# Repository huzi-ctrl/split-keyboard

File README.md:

# PKB — Wireless Split Mechanical Keyboard

**PKB (Printed KeyBoard)** is a custom 42-key wireless split mechanical keyboard designed from scratch in KiCad 10 and SolidWorks, powered by dual **Seeed Studio XIAO nRF52840** microcontrollers running **ZMK Firmware**.

---

## Why I Made It & How It Works

### Why I Built PKB
Traditional keyboards force your wrists to angle inward and make your fingers stretch across 6+ rows to reach numbers, symbols, and navigation keys. I wanted to design a compact, fully wireless split keyboard where:
1. Each half can be positioned at shoulder width for natural ergonomics.
2. Every letter, symbol, bracket, arrow key, F-key, and Numpad key is within **one row of the home row** using 3 tap-dance layers (**126 effective key bindings** across 42 physical switches).
3. Both halves fit on a **single panelized PCB** connected by mouse-bite breakaway tabs (`BO1`–`BO3`) to make fabrication and assembly clean and cost-effective.

### How It Works
- **Microcontroller & Wireless Split (`Seeed Studio XIAO nRF52840`)**: Each half runs a XIAO nRF52840 (`U1`/`U2`). The left half acts as the central controller (connecting to up to 4 devices over Bluetooth Low Energy or USB-C), while the right half pairs wirelessly over BLE to the left half.
- **I2C GPIO Expansion (`PCF8574AP`)**: Because the XIAO nRF52840 has only 11 GPIO pins, the 5 matrix columns (`COL0`–`COL4`) are driven directly by the XIAO (`D1`–`D5`), while the 5 matrix rows (`ROW0`–`ROW4`) are read through an **NXP PCF8574AP** 8-bit I2C I/O expander (`U3`/`U4`) on a shared I2C bus (`SCL` on `D9`, `SDA` on `D10`).
- **Dual 128×32 OLED Status Displays (`J3`/`J4`)**: Each half includes an I2C SSD1306 128×32 OLED display showing live battery percentage (`%`), active layer name (`QWERTY`, `CODE / NAV`, `NUM / FN`), and USB/Bluetooth profile status, with automatic 30-second idle blanking.
- **Per-Key RGB Underglow (`42× SK6812MINI`) with High-Side MOSFET Power Cut (`Q1`–`Q4`)**: Each half features 21 addressable SK6812MINI LEDs driven by hardware SPI (`D0`) and powered from `VBAT` through an NMOS+PMOS (`Q1`/`Q3`, `Q2`/`Q4`) high-side load switch (`D8`) so LED quiescent draw can be completely cut off to preserve battery life.

---

## PCB & 3D Renders

### Full Panelized PCB Layout (KiCad)

### 3D PCB Render

---

## Schematics

Both the left and right halves share a modular hierarchical schematic (`side.kicad_sch`):

### Left Half Schematic (`/left/`)

### Right Half Schematic (`/right/`)

---

## CAD & Enclosure Design

Custom 3D-printed enclosures modeled in SolidWorks with integrated battery compartment and cable routing channel (available in `.STEP`, `.SLDPRT`, and `.3MF` formats inside [`CAD/`](CAD/)):

| Left Half Enclosure (`left_cad.png`) | Right Half Enclosure (`right_cad.png`) |
| :---: | :---: |
|  |  |

---

## Hardware Pinout

| Function | XIAO nRF52840 Pin | Peripheral / Notes |
| :--- | :--- | :--- |
| **`DLED` (RGB Data)** | `D0` (`P0.02`) | 21× SK6812MINI addressable RGB LEDs per half (`&spi2` MOSI via 330 $\Omega$ resistor) |
| **`COL0` – `COL4`** | `D1` – `D5` (`P0.03`, `P0.28`, `P0.29`, `P0.04`, `P0.05`) | Matrix column outputs (`GPIO_ACTIVE_LOW`, `col2row`) |
| **`INT` (Expander Interrupt)** | `D6` (`P1.11`) | Connected to `PCF8574AP` `/INT` (Pin 13) |
| **`VLED` Power Switch** | `D8` (`P1.13`) | Drives NMOS $\rightarrow$ PMOS high-side switch for `VLED` (`ext-power`) |
| **`SCL` (I2C Clock)** | `D9` (`P1.14`) | `i2c0` (`&xiao_i2c`) with 4.7 k$\Omega$ pull-up to `+3V3` |
| **`SDA` (I2C Data)** | `D10` (`P1.15`) | `i2c0` (`&xiao_i2c`) with 4.7 k$\Omega$ pull-up to `+3V3` |
| **`ROW0` – `ROW4`** | `PCF8574AP` `P0` – `P4` | I2C I/O Expander at address `0x38` (`A0=A1=A2=GND`) |
| **OLED Display (`J3`/`J4`)** | I2C (`SCL`/`SDA`) | 128×32 SSD1306 OLED at address `0x3C` |

---

## Firmware & Keymap (`ZMK`)

Pre-built `.uf2` firmware binaries are automatically compiled by GitHub Actions and published to [**GitHub Releases**](https://github.com/huzi-ctrl/zmk-config-split-keyboard/releases/latest):
- **Left Half (Central):** `pkb_left-seeeduino_xiao_ble-zmk.uf2`
- **Right Half (Peripheral):** `pkb_right-seeeduino_xiao_ble-zmk.uf2`

### Tap-Dance Thumb Keys
- **Left Thumb**: `1 Tap` = **Space** | `2 Taps` = Toggle **Layer 1 (`CODE / NAV`)**
- **Right Thumb**: `1 Tap` = **Backspace** | `2 Taps` = Toggle **Layer 2 (`NUM / FN`)**

### Layer 0: `QWERTY` (Base)
```text
+-----------------------------------------+   +-----------------------------------------+
|   Q   |   W   |   E   |   R   |   T     |   |   Y   |   U   |   I   |   O   |   P     |
|   A   |   S   |   D   |   F   |   G     |   |   H   |   J   |   K   |   L   |   ;     |
|   Z   |   X   |   C   |   V   |   B     |   |   N   |   M   |   ,   |   .   |   /     |
| LCTRL | LSHFT | LALT  | LGUI  |  ESC    |   | RGUI  | RALT  | RSHFT | RCTRL | ENTER   |
+-------------------------------+---------+   +---------+-------------------------------+
                                | SPC/NAV |   | BSP/NUM |
                                +---------+   +---------+
```

### Layer 1: `CODE / NAV` (Double-Tap Left Thumb)
```text
+-----------------------------------------+   +-----------------------------------------+
|   `   |   [   |   ]   |   -   |   =     |   | PG_UP | HOME  |  UP   |  END  |  DEL    |
|   ~   |   {   |   }   |   _   |   +     |   | PG_DN | LEFT  | DOWN  | RIGHT |  ---    |
|  ---  |   \   |   |   |   <   |   >     |   |  ---  |  ---  |  ---  |  ---  |  ---    |
|  ---  |  ---  |  ---  |  ---  |  ---    |   |  ---  |  ---  |  ---  |  ---  |  ---    |
+-------------------------------+---------+   +---------+-------------------------------+
                                | SPC/NAV |   |   ---   |
                                +---------+   +---------+
```

### Layer 2: `NUM / FN` (Double-Tap Right Thumb)
```text
+-----------------------------------------+   +-----------------------------------------+
|  F1   |  F2   |  F3   |  F4   |  F5     |   |   /   |   7   |   8   |   9   |   -     |
|  F6   |  F7   |  F8   |  F9   |  F10    |   |   *   |   4   |   5   |   6   |   +     |
|  F11  |  F12  |RGB_TOG|EP_TOG |OUT_TOG  |   |   0   |   1   |   2   |   3   |   .     |
| BT 1  | BT 2  | BT 3  | BT 4  | BT_CLR  |   |  ---  |  ---  |  ---  |  ---  |  ---    |
+-------------------------------+---------+   +---------+-------------------------------+
                                |   ---   |   | BSP/NUM |
                                +---------+   +---------+
```

---

## Build & Assembly Guide

### Step 1: Depanelize the PCB
1. The left and right keyboard halves are manufactured as a single panel joined by three mouse-bite breakaway tabs (`BO1`, `BO2`, `BO3`) along the center spine.
2. Gently flex or snip along the perforated mouse-bite slots using flush cutters to separate the **Left** and **Right** PCBs, then lightly sand the tab edges flush.

### Step 2: Solder Reverse-Mount RGB LEDs (`D63`–`D104`)
1. Flip the PCB to the **bottom (`B.Cu`)** layer.
2. Solder the 21× **SK6812MINI-E** reverse-mount addressable RGB LEDs per half so their lenses shine upward through the rectangular switch LED cutouts.
   - **Important**: Align the notched/beveled corner (`Pin 3 = GND`) of each SK6812MINI-E with the silkscreen marker on the PCB.
   - Use a temperature-controlled soldering iron at **$280\text{--}300\,^\circ\text{C}$** (or low-temp solder paste + hot air) to avoid overheating the plastic LED packages.

### Step 3: Solder Matrix Diodes (`D1`–`D42`) & SMD MOSFETs (`Q1`–`Q4`)
1. **Matrix Diodes (`D1`–`D42`)**: The `ComboDiode` footprints support either **1N4148W (SOD-123 SMD)** diodes on `F.Cu` or `B.Cu`, or **1N4148 (DO-35 through-hole)** diodes. Orient every diode's cathode band (`|◁`) toward the square pad (`K`).
2. **High-Side LED Power Switch (`Q1`–`Q4`)**: Solder the SOT-23 NMOS (`Q1`, `Q2`) and PMOS (`Q3`, `Q4`) transistors onto their designated SMD pads near the microcontroller area on each half.

### Step 4: Solder Passive Components & IC Expanders (`U3`, `U4`)
1. Solder the **100 nF decoupling capacitors** (`C1`–`C42`) next to each RGB LED, plus the **100 µF bulk radial capacitors** (`C43`, `C44`) across the `VLED` power rails.
2. Solder the axial resistors on each half:
   - **$4.7\text{ k}\Omega$** (`R1`–`R6`): I2C `SDA`/`SCL` pull-ups and `/INT` pull-ups.
   - **$10\text{ k}\Omega$** (`R7`, `R8`) & **$100\text{ k}\Omega$** (`R9`, `R10`): MOSFET gate bias/pull-down resistors.
   - **$330\text{ }\Omega$** (`R11`, `R12`): RGB `DIN` data-line series resistors.
3. Solder the **PCF8574AP** DIP-16 I2C I/O expanders (`U3`, `U4`)—or DIP-16 IC sockets—ensuring the Pin 1 half-moon notch matches the PCB silkscreen.

### Step 5: Solder Hot-Swap Sockets, Switches & Peripherals
1. **Kailh MX Hot-Swap Sockets (`SW1`–`SW42`)**: On the **bottom (`B.Cu`)** side of the PCB, solder all 42 Kailh Choc/MX hot-swap sockets onto their wide SMD pads, making sure they sit flat against the board and do not obstruct the switch center hole.
2. **Seeed Studio XIAO nRF52840 (`U1`, `U2`)**:
   - Before soldering the XIAO down, solder two short wire leads onto the **battery `+` and `-` pads** on the underside of the XIAO nRF52840 and route them to the PCB's battery input pads (`J1`/`J2`) and slide power switch (`SW43`/`SW44`).
   - Solder the XIAO nRF52840 onto the PCB using pin headers or low-profile Mill-Max sockets with the USB-C port facing outward toward the top edge of the board.
3. **128×32 SSD1306 OLED Display (`J3`, `J4`)**: Solder the 4-pin OLED header (`GND`, `VCC`, `SCL`, `SDA`) so the OLED sits above the XIAO footprint.
4. **Slide Power Switch (`SW43`, `SW44`) & LiPo Battery (`J1`, `J2`)**: Solder the 3-pin slide switch and the 2-pin JST-PH 2.0 mm battery connector.

### Step 6: Flash ZMK Firmware & Pair Halves
1. Download the latest `.uf2` files from [**GitHub Releases**](https://github.com/huzi-ctrl/zmk-config-split-keyboard/releases/latest):
   - `pkb_left-seeeduino_xiao_ble-zmk.uf2`
   - `pkb_right-seeeduino_xiao_ble-zmk.uf2`
2. Connect the **Left XIAO nRF52840** to your computer via USB-C and **double-click its onboard Reset button**—it will mount as a removable drive named `XIAO-SENSE`.
3. Drag and drop `pkb_left-seeeduino_xiao_ble-zmk.uf2` onto the drive. Repeat with `pkb_right-seeeduino_xiao_ble-zmk.uf2` on the **Right XIAO nRF52840**.
4. Power both halves on at the same time; they will automatically bond to each other over BLE. Pair your computer or phone to **`PKB`** via Bluetooth!

### Step 7: Final Case Assembly
1. 3D-print [`CAD/3mf/left.3MF`](CAD/3mf/left.3MF) and [`CAD/3mf/right.3MF`](CAD/3mf/right.3MF) in PLA or PETG (`0.2 mm` layer height, 15–20% infill).
2. Place the 3.7 V LiPo battery into the recessed pocket at the base of each printed enclosure and plug it into the JST-PH connector (`J1`/`J2`).
3. Seat the assembled PCB into the enclosure, secure it with M2 screws through the mounting holes, press your 42 MX mechanical switches into the hot-swap sockets, and install your keycaps!

---

## Repository Structure

```text
├── CAD/
│   ├── Keyboard.step          # Full 3D assembly in STEP format
│   ├── 3mf/                   # Printable 3MF files (left.3MF, right.3MF)
│   └── Raw/                   # Native SolidWorks part files (left.SLDPRT, right.SLDPRT)
├── kicad/
│   ├── Keyboard.kicad_pro     # KiCad 10 project file
│   ├── Keyboard.kicad_sch     # Top-level schematic sheet
│   ├── side.kicad_sch         # Left/Right modular keyboard half schematic
│   └── Keyboard.kicad_pcb     # Panelized 2-layer PCB layout
├── firmware/
│   ├── boards/shields/pkb/    # ZMK shield definition, devicetree, Kconfig, and C init
│   ├── config/                # Keymap and ZMK configuration
│   └── build.yaml             # GitHub Actions build matrix
├── images/                    # PCB, schematic, and CAD screenshots
└── production.zip             # Ready-to-manufacture Gerber, Drill, and CPL files
```

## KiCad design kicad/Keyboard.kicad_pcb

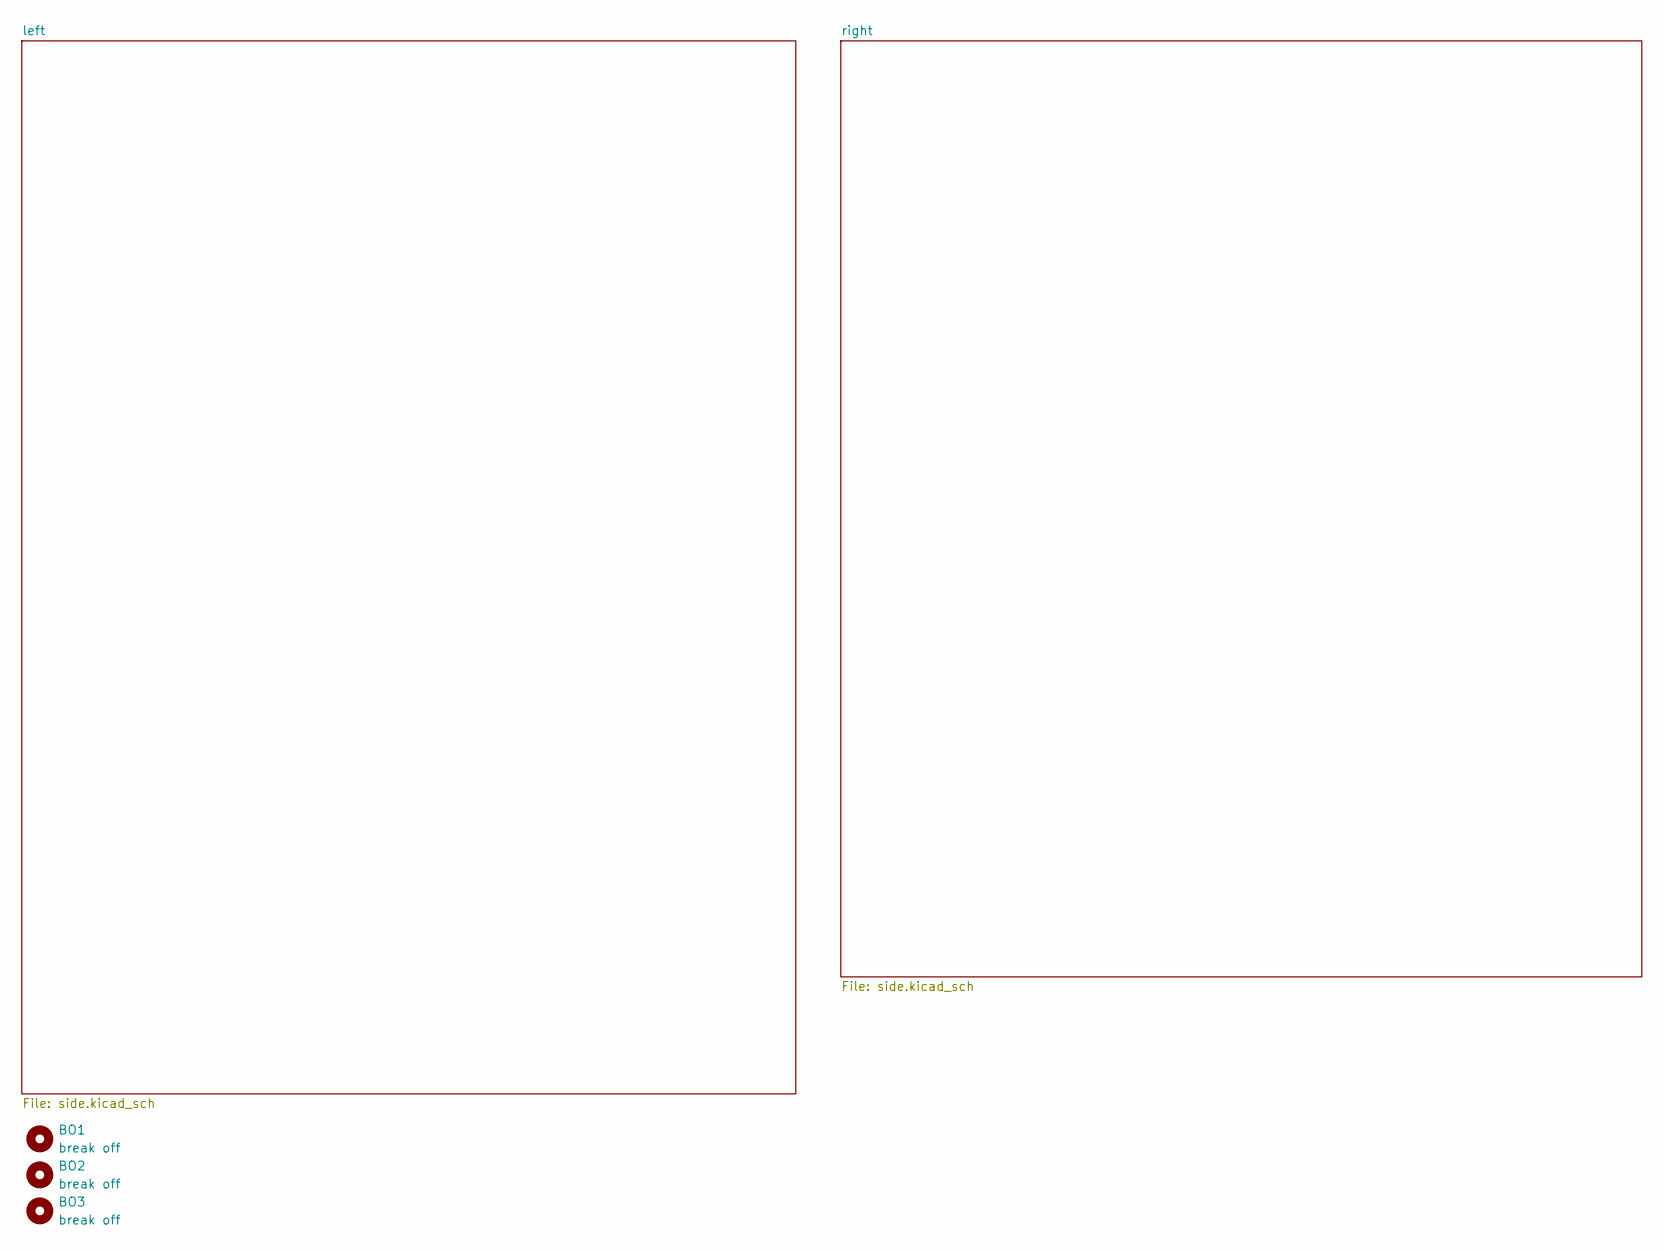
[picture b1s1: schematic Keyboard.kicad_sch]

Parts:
BO1, BO2, BO3: break off; MouseBite-Slot_2.0x4.5mm_outset_D0.5mm_P0.85mm_7h

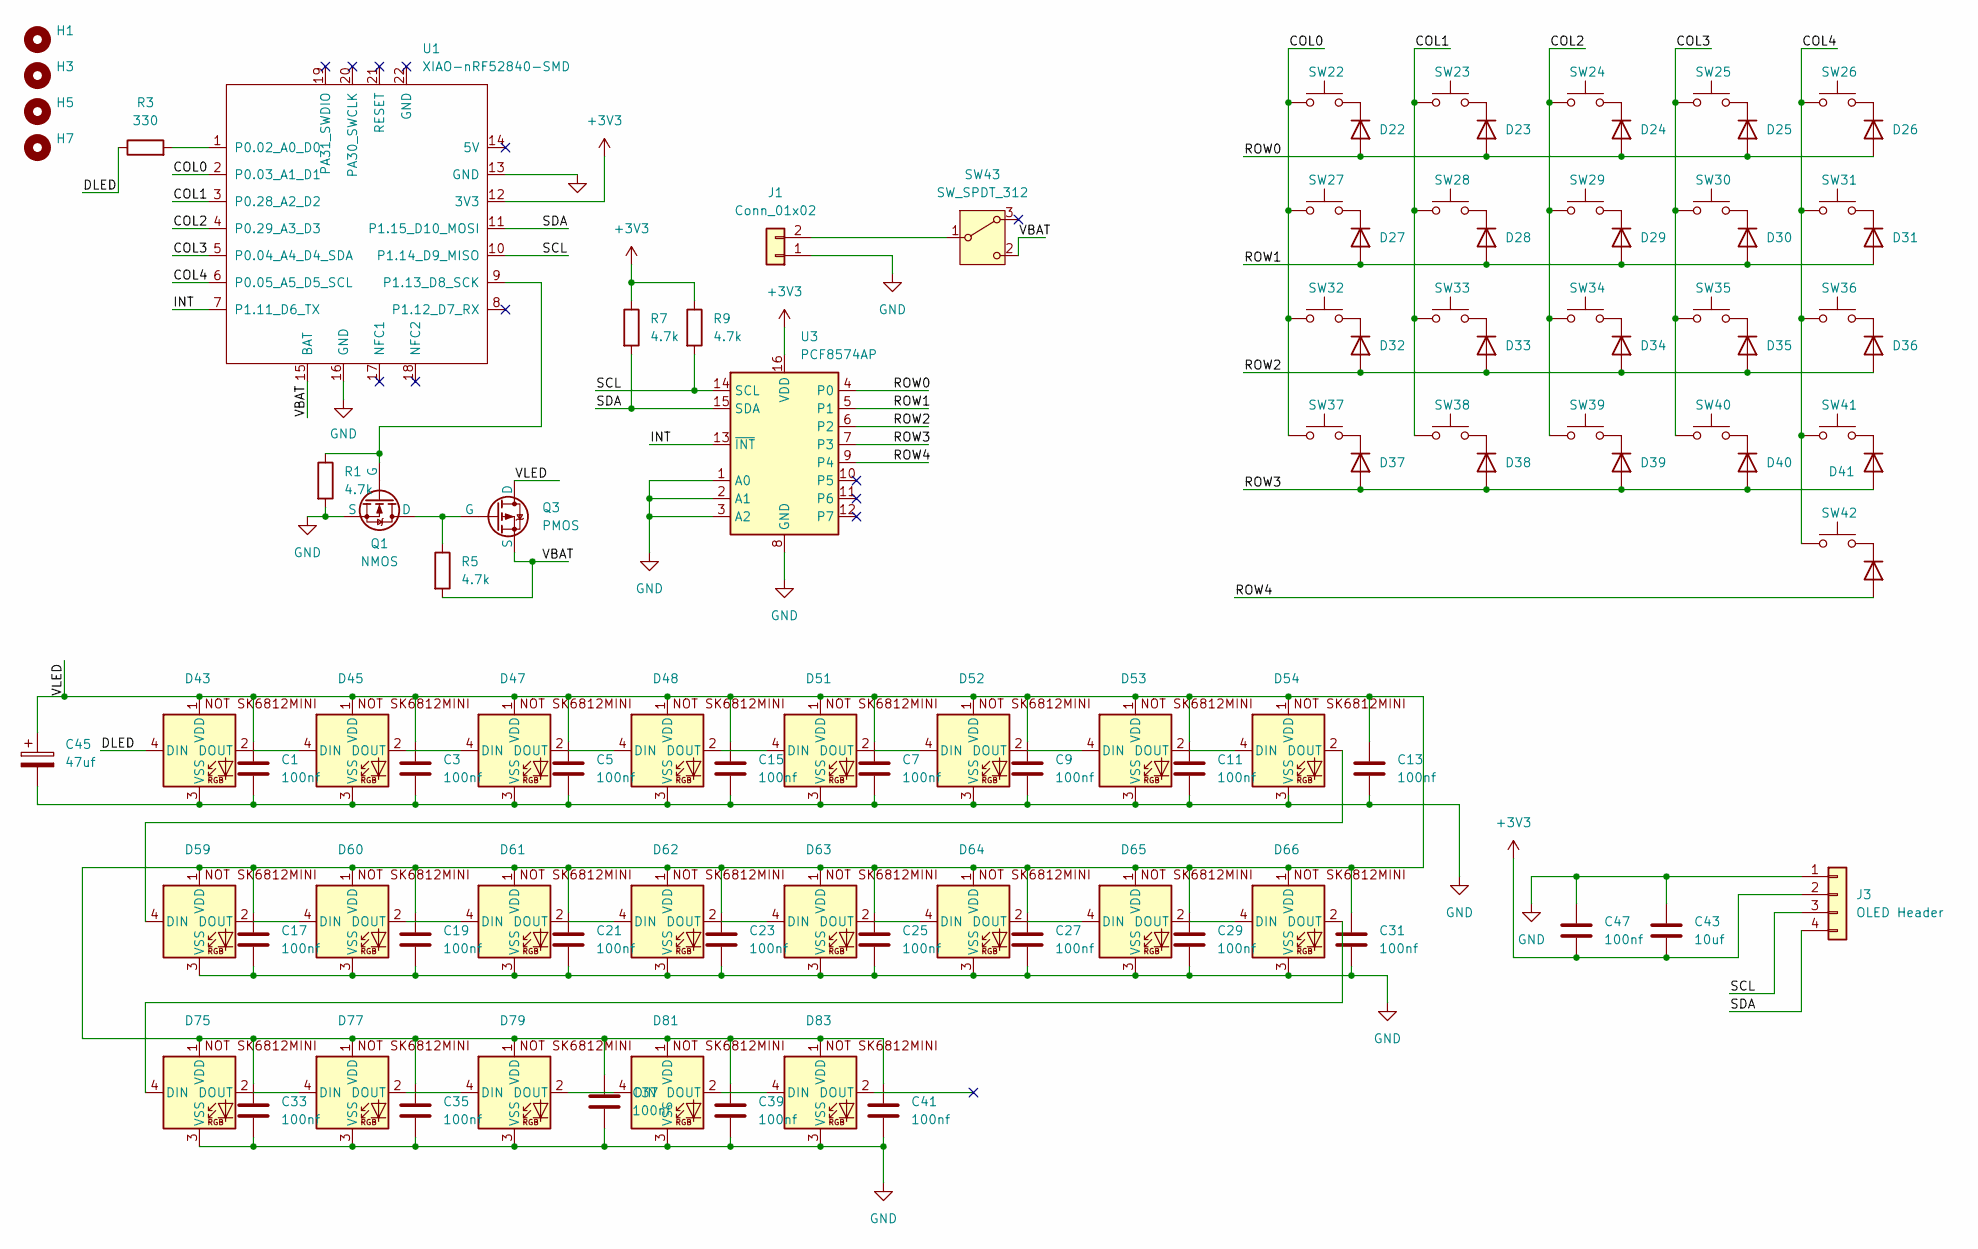
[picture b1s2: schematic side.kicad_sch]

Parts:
C1, C3, C5, C7, C9, C11, C13, C15, C17, C19, C21, C23, C25, C27, C29, C31, C33, C35, C37, C39, C41, C47: 100nf; C_Disc_D5.0mm_W2.5mm_P5.00mm
C43: 10uf; C_Disc_D5.0mm_W2.5mm_P5.00mm
C45: 47uf; CP_Radial_D8.0mm_P3.50mm
D22, D23, D24, D25, D26, D27, D28, D29, D30, D31, D32, D33, D34, D35, D36, D37, D38, D39, D40, D41, D42: D
D43, D45, D47, D48, D51, D52, D53, D54, D59, D60, D61, D62, D63, D64, D65, D66, D75, D77, D79, D81, D83: SK6812MINI-E
H1, H3, H5, H7: MountingHole; MountingHole_2.2mm_M2
J1: Conn_01x02; JST_PH_S2B-PH-K_1x02_P2.00mm_Horizontal
J3: OLED Header; PinSocket_1x04_P2.54mm_Vertical
Q1: NMOS; TO-92-2_Wide
Q3: PMOS; TO-220-3_Vertical
R1, R5, R7, R9: 4.7k; R_Axial_DIN0207_L6.3mm_D2.5mm_P10.16mm_Horizontal
R3: 330; R_Axial_DIN0207_L6.3mm_D2.5mm_P10.16mm_Horizontal
SW22, SW23, SW24, SW25, SW26, SW27, SW28, SW29, SW30, SW31, SW32, SW33, SW34, SW35, SW36, SW37, SW38, SW39, SW40, SW41, SW42: SW_Push
SW43: SW_SPDT_312; PinHeader_1x03_P2.54mm_Vertical
U1: XIAO-nRF52840-SMD; modified-XIAO-nRF52840-SMD
U3: PCF8574AP; DIP-16_W7.62mm

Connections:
+3V3: C43.2, C47.2, J3.2, R7.1, R9.1, U1.12 (3V3), U3.16 (VDD); also elsewhere on the board
/left/COL0: SW22.1, SW27.1, SW32.1, SW37.1, U1.2 (P0.03_A1_D1)
/left/COL1: SW23.1, SW28.1, SW33.1, SW38.1, U1.3 (P0.28_A2_D2)
/left/COL2: SW24.1, SW29.1, SW34.1, SW39.1, U1.4 (P0.29_A3_D3)
/left/COL3: SW25.1, SW30.1, SW35.1, SW40.1, U1.5 (P0.04_A4_D4_SDA)
/left/COL4: SW26.1, SW31.1, SW36.1, SW41.1, SW42.1, U1.6 (P0.05_A5_D5_SCL)
/left/DLED: D43.4 (DIN), R3.1
/left/INT: U1.7 (P1.11_D6_TX), U3.13 (~INT)
/left/ROW0: D22.2 (A), D23.2 (A), D24.2 (A), D25.2 (A), D26.2 (A), U3.4 (P0)
/left/ROW1: D27.2 (A), D28.2 (A), D29.2 (A), D30.2 (A), D31.2 (A), U3.5 (P1)
/left/ROW2: D32.2 (A), D33.2 (A), D34.2 (A), D35.2 (A), D36.2 (A), U3.6 (P2)
/left/ROW3: D37.2 (A), D38.2 (A), D39.2 (A), D40.2 (A), D41.2 (A), U3.7 (P3)
/left/ROW4: D42.2 (A), U3.9 (P4)
/left/SCL: J3.3, R9.2, U1.10 (P1.14_D9_MISO), U3.14 (SCL)
/left/SDA: J3.4, R7.2, U1.11 (P1.15_D10_MOSI), U3.15 (SDA)
/left/VBAT: Q3.3 (S), R5.2, SW43.2 (C), U1.15 (BAT)
/left/VLED: C1.1, C3.1, C5.1, C7.1, C9.1, C11.1, C13.1, C15.1, C17.1, C19.1, C21.1, C23.1, C25.1, C27.1, C29.1, C31.1, C33.1, C35.1, C37.1, C39.1, C41.1, C45.1, D43.1 (VDD), D45.1 (VDD), D47.1 (VDD), D48.1 (VDD), D51.1 (VDD), D52.1 (VDD), D53.1 (VDD), D54.1 (VDD), D59.1 (VDD), D60.1 (VDD), D61.1 (VDD), D62.1 (VDD), D63.1 (VDD), D64.1 (VDD), D65.1 (VDD), D66.1 (VDD), D75.1 (VDD), D77.1 (VDD), D79.1 (VDD), D81.1 (VDD), D83.1 (VDD), Q3.1 (D)
GND: C1.2, C3.2, C5.2, C7.2, C9.2, C11.2, C13.2, C15.2, C17.2, C19.2, C21.2, C23.2, C25.2, C27.2, C29.2, C31.2, C33.2, C35.2, C37.2, C39.2, C41.2, C43.1, C45.2, C47.1, D43.3 (VSS), D45.3 (VSS), D47.3 (VSS), D48.3 (VSS), D51.3 (VSS), D52.3 (VSS), D53.3 (VSS), D54.3 (VSS), D59.3 (VSS), D60.3 (VSS), D61.3 (VSS), D62.3 (VSS), D63.3 (VSS), D64.3 (VSS), D65.3 (VSS), D66.3 (VSS), D75.3 (VSS), D77.3 (VSS), D79.3 (VSS), D81.3 (VSS), D83.3 (VSS), J1.1, J3.1, Q1.3 (S), R1.2, U1.13 (GND), U1.16 (GND), U3.1 (A0), U3.2 (A1), U3.3 (A2), U3.8 (GND); also elsewhere on the board
unnamed: D22.1 (K), SW22.2
unnamed: D23.1 (K), SW23.2
unnamed: D24.1 (K), SW24.2
unnamed: D25.1 (K), SW25.2
unnamed: D26.1 (K), SW26.2
unnamed: D27.1 (K), SW27.2
unnamed: D28.1 (K), SW28.2
unnamed: D29.1 (K), SW29.2
unnamed: D30.1 (K), SW30.2
unnamed: D31.1 (K), SW31.2
unnamed: D32.1 (K), SW32.2
unnamed: D33.1 (K), SW33.2
unnamed: D34.1 (K), SW34.2
unnamed: D35.1 (K), SW35.2
unnamed: D36.1 (K), SW36.2
unnamed: D37.1 (K), SW37.2
unnamed: D38.1 (K), SW38.2
unnamed: D39.1 (K), SW39.2
unnamed: D40.1 (K), SW40.2
unnamed: D41.1 (K), SW41.2
unnamed: D42.1 (K), SW42.2
unnamed: D43.2 (DOUT), D45.4 (DIN)
unnamed: D45.2 (DOUT), D47.4 (DIN)
unnamed: D47.2 (DOUT), D48.4 (DIN)
unnamed: D48.2 (DOUT), D51.4 (DIN)
unnamed: D51.2 (DOUT), D52.4 (DIN)
unnamed: D52.2 (DOUT), D53.4 (DIN)
unnamed: D53.2 (DOUT), D54.4 (DIN)
unnamed: D54.2 (DOUT), D59.4 (DIN)
unnamed: D59.2 (DOUT), D60.4 (DIN)
unnamed: D60.2 (DOUT), D61.4 (DIN)
unnamed: D61.2 (DOUT), D62.4 (DIN)
unnamed: D62.2 (DOUT), D63.4 (DIN)
unnamed: D63.2 (DOUT), D64.4 (DIN)
unnamed: D64.2 (DOUT), D65.4 (DIN)
unnamed: D65.2 (DOUT), D66.4 (DIN)
unnamed: D66.2 (DOUT), D75.4 (DIN)
unnamed: D75.2 (DOUT), D77.4 (DIN)
unnamed: D77.2 (DOUT), D79.4 (DIN)
unnamed: D79.2 (DOUT), D81.4 (DIN)
unnamed: D81.2 (DOUT), D83.4 (DIN)
unnamed: J1.2, SW43.1 (B)
unnamed: Q1.1 (D), Q3.2 (G), R5.1
unnamed: Q1.2 (G), R1.1, U1.9 (P1.13_D8_SCK)
unnamed: R3.2, U1.1 (P0.02_A0_D0)

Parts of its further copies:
C2, C4, C6, C8, C10, C12, C14, C16, C18, C20, C22, C24, C26, C28, C30, C32, C34, C36, C38, C40, C42, C48: 100nf; C_Disc_D5.0mm_W2.5mm_P5.00mm
C44: 10uf; C_Disc_D5.0mm_W2.5mm_P5.00mm
C46: 47uf; CP_Radial_D8.0mm_P3.50mm
D1, D2, D3, D4, D5, D6, D7, D8, D9, D10, D11, D12, D13, D14, D15, D16, D17, D18, D19, D20, D21: D
D44, D46, D49, D50, D55, D56, D57, D58, D67, D68, D69, D70, D71, D72, D73, D74, D91, D93, D95, D97, D99: SK6812MINI-E
H2, H4, H6, H8: MountingHole; MountingHole_2.2mm_M2
J2: Conn_01x02; JST_PH_S2B-PH-K_1x02_P2.00mm_Horizontal
J4: OLED Header; PinSocket_1x04_P2.54mm_Vertical
Q2: NMOS; TO-92-2_Wide
Q4: PMOS; TO-220-3_Vertical
R2, R6, R8, R10: 4.7k; R_Axial_DIN0207_L6.3mm_D2.5mm_P10.16mm_Horizontal
R4: 330; R_Axial_DIN0207_L6.3mm_D2.5mm_P10.16mm_Horizontal
SW1, SW2, SW3, SW4, SW5, SW6, SW7, SW8, SW9, SW10, SW11, SW12, SW13, SW14, SW15, SW16, SW17, SW18, SW19, SW20, SW21: SW_Push
SW44: SW_SPDT_312; PinHeader_1x03_P2.54mm_Vertical
U2: XIAO-nRF52840-SMD; modified-XIAO-nRF52840-SMD
U4: PCF8574AP; DIP-16_W7.62mm

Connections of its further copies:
+3V3: C44.2, C48.2, J4.2, R8.1, R10.1, U2.12 (3V3), U4.16 (VDD); also elsewhere on the board
/right/COL0: SW1.1, SW6.1, SW11.1, SW16.1, U2.2 (P0.03_A1_D1)
/right/COL1: SW2.1, SW7.1, SW12.1, SW17.1, U2.3 (P0.28_A2_D2)
/right/COL2: SW3.1, SW8.1, SW13.1, SW18.1, U2.4 (P0.29_A3_D3)
/right/COL3: SW4.1, SW9.1, SW14.1, SW19.1, U2.5 (P0.04_A4_D4_SDA)
/right/COL4: SW5.1, SW10.1, SW15.1, SW20.1, SW21.1, U2.6 (P0.05_A5_D5_SCL)
/right/DLED: D44.4 (DIN), R4.1
/right/INT: U2.7 (P1.11_D6_TX), U4.13 (~INT)
/right/ROW0: D1.2 (A), D2.2 (A), D3.2 (A), D4.2 (A), D5.2 (A), U4.4 (P0)
/right/ROW1: D6.2 (A), D7.2 (A), D8.2 (A), D9.2 (A), D10.2 (A), U4.5 (P1)
/right/ROW2: D11.2 (A), D12.2 (A), D13.2 (A), D14.2 (A), D15.2 (A), U4.6 (P2)
/right/ROW3: D16.2 (A), D17.2 (A), D18.2 (A), D19.2 (A), D20.2 (A), U4.7 (P3)
/right/ROW4: D21.2 (A), U4.9 (P4)
/right/SCL: J4.3, R10.2, U2.10 (P1.14_D9_MISO), U4.14 (SCL)
/right/SDA: J4.4, R8.2, U2.11 (P1.15_D10_MOSI), U4.15 (SDA)
/right/VBAT: Q4.3 (S), R6.2, SW44.2 (C), U2.15 (BAT)
/right/VLED: C2.1, C4.1, C6.1, C8.1, C10.1, C12.1, C14.1, C16.1, C18.1, C20.1, C22.1, C24.1, C26.1, C28.1, C30.1, C32.1, C34.1, C36.1, C38.1, C40.1, C42.1, C46.1, D44.1 (VDD), D46.1 (VDD), D49.1 (VDD), D50.1 (VDD), D55.1 (VDD), D56.1 (VDD), D57.1 (VDD), D58.1 (VDD), D67.1 (VDD), D68.1 (VDD), D69.1 (VDD), D70.1 (VDD), D71.1 (VDD), D72.1 (VDD), D73.1 (VDD), D74.1 (VDD), D91.1 (VDD), D93.1 (VDD), D95.1 (VDD), D97.1 (VDD), D99.1 (VDD), Q4.1 (D)
GND: C2.2, C4.2, C6.2, C8.2, C10.2, C12.2, C14.2, C16.2, C18.2, C20.2, C22.2, C24.2, C26.2, C28.2, C30.2, C32.2, C34.2, C36.2, C38.2, C40.2, C42.2, C44.1, C46.2, C48.1, D44.3 (VSS), D46.3 (VSS), D49.3 (VSS), D50.3 (VSS), D55.3 (VSS), D56.3 (VSS), D57.3 (VSS), D58.3 (VSS), D67.3 (VSS), D68.3 (VSS), D69.3 (VSS), D70.3 (VSS), D71.3 (VSS), D72.3 (VSS), D73.3 (VSS), D74.3 (VSS), D91.3 (VSS), D93.3 (VSS), D95.3 (VSS), D97.3 (VSS), D99.3 (VSS), J2.1, J4.1, R2.2, U2.13 (GND), U2.16 (GND), U4.1 (A0), U4.2 (A1), U4.3 (A2), U4.8 (GND); also elsewhere on the board
unnamed: D1.1 (K), SW1.2
unnamed: D2.1 (K), SW2.2
unnamed: D3.1 (K), SW3.2
unnamed: D4.1 (K), SW4.2
unnamed: D5.1 (K), SW5.2
unnamed: D6.1 (K), SW6.2
unnamed: D7.1 (K), SW7.2
unnamed: D8.1 (K), SW8.2
unnamed: D9.1 (K), SW9.2
unnamed: D10.1 (K), SW10.2
unnamed: D11.1 (K), SW11.2
unnamed: D12.1 (K), SW12.2
unnamed: D13.1 (K), SW13.2
unnamed: D14.1 (K), SW14.2
unnamed: D15.1 (K), SW15.2
unnamed: D16.1 (K), SW16.2
unnamed: D17.1 (K), SW17.2
unnamed: D18.1 (K), SW18.2
unnamed: D19.1 (K), SW19.2
unnamed: D20.1 (K), SW20.2
unnamed: D21.1 (K), SW21.2
unnamed: D44.2 (DOUT), D46.4 (DIN)
unnamed: D46.2 (DOUT), D49.4 (DIN)
unnamed: D49.2 (DOUT), D50.4 (DIN)
unnamed: D50.2 (DOUT), D55.4 (DIN)
unnamed: D55.2 (DOUT), D56.4 (DIN)
unnamed: D56.2 (DOUT), D57.4 (DIN)
unnamed: D57.2 (DOUT), D58.4 (DIN)
unnamed: D58.2 (DOUT), D67.4 (DIN)
unnamed: D67.2 (DOUT), D68.4 (DIN)
unnamed: D68.2 (DOUT), D69.4 (DIN)
unnamed: D69.2 (DOUT), D70.4 (DIN)
unnamed: D70.2 (DOUT), D71.4 (DIN)
unnamed: D71.2 (DOUT), D72.4 (DIN)
unnamed: D72.2 (DOUT), D73.4 (DIN)
unnamed: D73.2 (DOUT), D74.4 (DIN)
unnamed: D74.2 (DOUT), D91.4 (DIN)
unnamed: D91.2 (DOUT), D93.4 (DIN)
unnamed: D93.2 (DOUT), D95.4 (DIN)
unnamed: D95.2 (DOUT), D97.4 (DIN)
unnamed: D97.2 (DOUT), D99.4 (DIN)
unnamed: J2.2, SW44.1 (B)
unnamed: Q2.1 (D), Q4.2 (G), R6.1
unnamed: Q2.2 (G), R2.1, U2.9 (P1.13_D8_SCK)
unnamed: R4.2, U2.1 (P0.02_A0_D0)

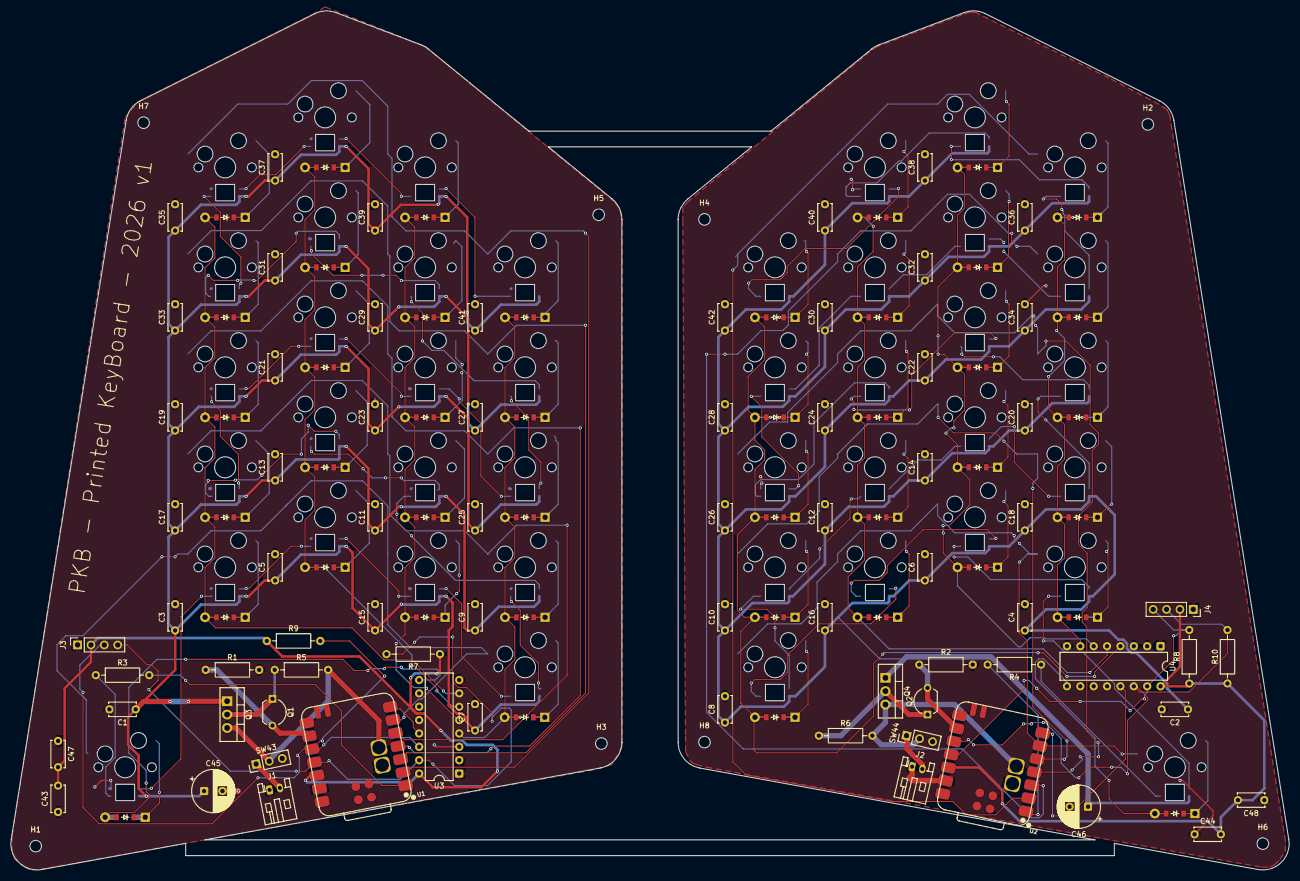
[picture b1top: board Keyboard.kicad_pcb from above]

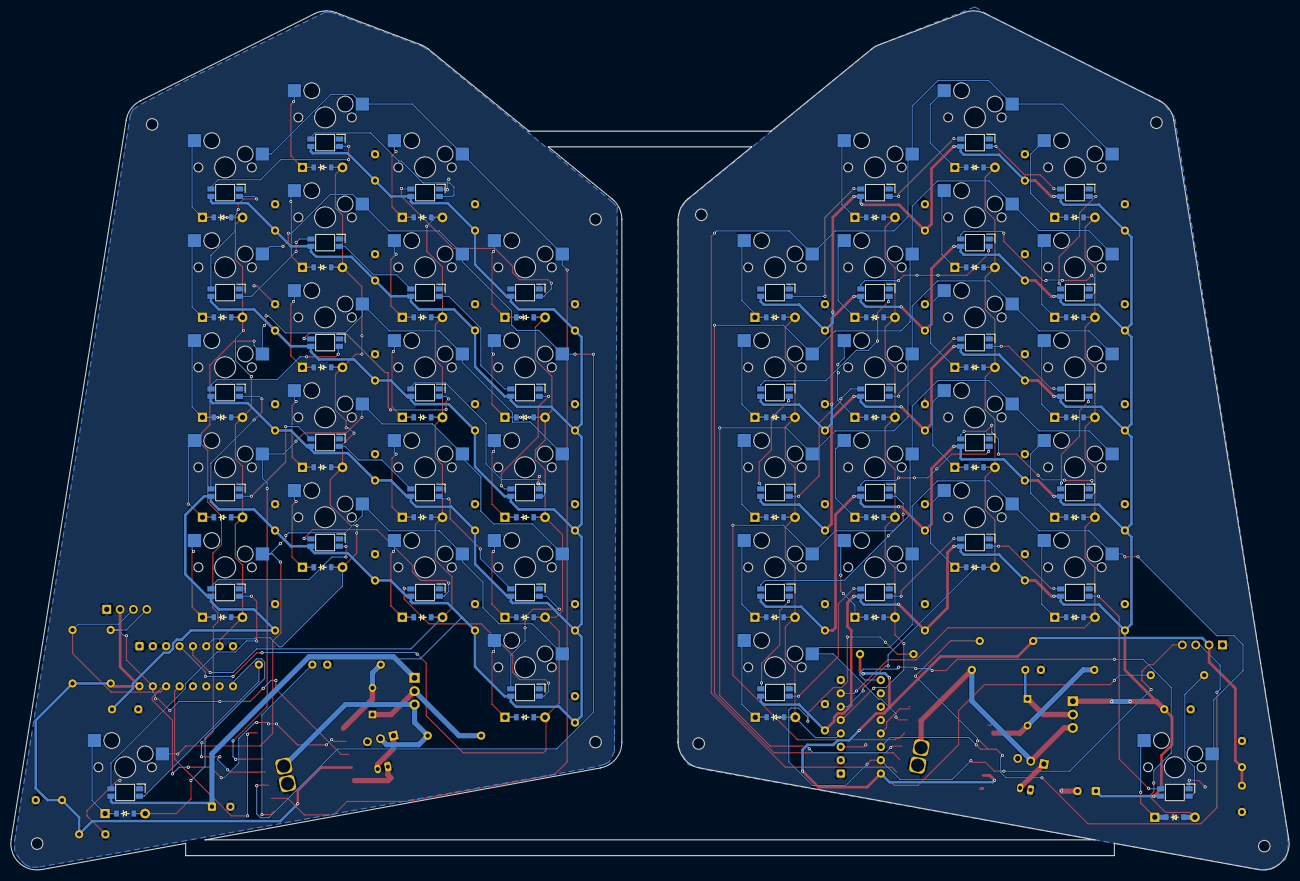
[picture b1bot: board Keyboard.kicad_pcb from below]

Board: 2 copper layers, 242.9 x 163.3 mm, 206 parts (42 on the bottom side), 124 nets.

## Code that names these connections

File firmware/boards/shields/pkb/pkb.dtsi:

// This file was generated from a template. Edit it to match your keyboard.
// See https://zmk.dev/docs/development/hardware-integration/new-shield for more
// instructions.

#include <dt-bindings/zmk/matrix_transform.h>
#include <dt-bindings/led/led.h>

/ {
    chosen {
        zephyr,display = &oled;
        zmk,kscan = &kscan0;
        zmk,physical-layout = &default_layout;
        zmk,underglow = &led_strip;
    };

    default_layout: physical_layout0 {
        compatible = "zmk,physical-layout";
        display-name = "PKB 40% Standard";
        transform = <&default_transform>;
    };

    kscan0: kscan0 {
        compatible = "zmk,kscan-gpio-matrix";
        // With D1..D21 flipped (Anode on ROW, Cathode on COL):
        // XIAO drives COL0..COL4 active-low (0V when active) and PCF8574AP
        // reads ROW0..ROW4 active-low (pulled high to +3.3V internally by PCF8574AP).
        diode-direction = "col2row";
        wakeup-source;

        row-gpios
            = <&pcf8574 0 GPIO_ACTIVE_LOW> // ROW0 -> U4 P0 (Pin 4)
            , <&pcf8574 1 GPIO_ACTIVE_LOW> // ROW1 -> U4 P1 (Pin 5)
            , <&pcf8574 2 GPIO_ACTIVE_LOW> // ROW2 -> U4 P2 (Pin 6)
            , <&pcf8574 3 GPIO_ACTIVE_LOW> // ROW3 -> U4 P3 (Pin 7)
            , <&pcf8574 4 GPIO_ACTIVE_LOW> // ROW4 -> U4 P4 (Pin 9)
            ;
    };

    default_transform: keymap_transform_0 {
        compatible = "zmk,matrix-transform";
        columns = <10>; // 5 columns on the left + 5 columns on the right
        rows = <5>;     // 4 main rows + 1 extra row for the thumb key

        map = <
        // Left Half (Cols 0-4)                      // Right Half (Cols 5-9)
        RC(0,0) RC(0,1) RC(0,2) RC(0,3) RC(0,4)      RC(0,9) RC(0,8) RC(0,7) RC(0,6) RC(0,5)
        RC(1,0) RC(1,1) RC(1,2) RC(1,3) RC(1,4)      RC(1,9) RC(1,8) RC(1,7) RC(1,6) RC(1,5)
        RC(2,0) RC(2,1) RC(2,2) RC(2,3) RC(2,4)      RC(2,9) RC(2,8) RC(2,7) RC(2,6) RC(2,5)
        RC(3,0) RC(3,1) RC(3,2) RC(3,3) RC(3,4)      RC(3,9) RC(3,8) RC(3,7) RC(3,6) RC(3,5)
                                        RC(4,4)      RC(4,9)
        >;
    };

    ext-power {
        compatible = "zmk,ext-power-generic";
        // P1.13_D8_SCK (Pin 9) drives Q2 (NMOS) -> Q4 (PMOS) to switch VBAT to VLED
        control-gpios = <&xiao_d 8 GPIO_ACTIVE_HIGH>;
    };
};

&pinctrl {
    // I2C0 (xiao_i2c) remapped from D4/D5 (used by COL3/COL4) to D9 (SCL) and D10 (SDA)
    i2c0_default: i2c0_default {
        group1 {
            psels = <NRF_PSEL(TWIM_SDA, 1, 15)>, // P1.15_D10_MOSI (Pin 11) -> SDA
                    <NRF_PSEL(TWIM_SCL, 1, 14)>; // P1.14_D9_MISO  (Pin 10) -> SCL
        };
    };
    i2c0_sleep: i2c0_sleep {
        group1 {
            psels = <NRF_PSEL(TWIM_SDA, 1, 15)>,
                    <NRF_PSEL(TWIM_SCL, 1, 14)>;
            low-power-enable;
        };
    };

    // SPI2 MOSI mapped to P0.02_A0_D0 (Pin 1) -> DLED via R4 (330 ohm)
    spi2_default: spi2_default {
        group1 {
            psels = <NRF_PSEL(SPIM_MOSI, 0, 2)>;
        };
    };
    spi2_sleep: spi2_sleep {
        group1 {
            psels = <NRF_PSEL(SPIM_MOSI, 0, 2)>;
            low-power-enable;
        };
    };
};

&xiao_i2c {
    status = "okay";
    pinctrl-0 = <&i2c0_default>;
    pinctrl-1 = <&i2c0_sleep>;
    pinctrl-names = "default", "sleep";
    clock-frequency = <I2C_BITRATE_STANDARD>;

    // U4: PCF8574AP with A0=A1=A2=GND -> I2C address 0x38
    // (Note: If using a non-'A' PCF8574 chip, change 0x38 to 0x20)
    pcf8574: pcf8574@38 {
        compatible = "nxp,pcf8574";
        status = "okay";
        reg = <0x38>;
        gpio-controller;
        #gpio-cells = <2>;
        ngpios = <8>;
        int-gpios = <&xiao_d 6 (GPIO_ACTIVE_LOW | GPIO_PULL_UP)>; // P1.11_D6_TX (Pin 7) -> INT
    };

    // J4: OLED Header (SSD1306 128x32)
    oled: ssd1306@3c {
        compatible = "solomon,ssd1306fb";
        reg = <0x3c>;
        width = <128>;
        height = <32>;
        segment-offset = <0>;
        page-offset = <0>;
        display-offset = <0>;
        multiplex-ratio = <31>;
        segment-remap;
        com-invdir;
        com-sequential;
        inversion-on;
        prechargep = <0x22>;
    };
};

&spi2 {
    compatible = "nordic,nrf-spim";
    status = "okay";
    pinctrl-0 = <&spi2_default>;
    pinctrl-1 = <&spi2_sleep>;
    pinctrl-names = "default", "sleep";

    led_strip: ws2812@0 {
        compatible = "worldsemi,ws2812-spi";
        reg = <0>;
        spi-max-frequency = <4000000>;
        chain-length = <21>; // 21 SK6812MINI LEDs per board half
        spi-one-frame = <0x70>;
        spi-zero-frame = <0x40>;
        color-mapping = <LED_COLOR_ID_GREEN LED_COLOR_ID_RED LED_COLOR_ID_BLUE>;
    };
};

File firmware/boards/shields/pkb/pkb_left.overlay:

// This file was generated from a template. Edit it to match your keyboard.
// See https://zmk.dev/docs/development/hardware-integration/new-shield for more
// instructions.

#include "pkb.dtsi"

&kscan0 {
    // COL0..COL4 on XIAO pins D1..D5 (active-low outputs for col2row scanning with PCF8574AP)
    col-gpios
        = <&xiao_d 1 GPIO_ACTIVE_LOW> // COL0 -> P0.03_A1_D1 (Pin 2)
        , <&xiao_d 2 GPIO_ACTIVE_LOW> // COL1 -> P0.28_A2_D2 (Pin 3)
        , <&xiao_d 3 GPIO_ACTIVE_LOW> // COL2 -> P0.29_A3_D3 (Pin 4)
        , <&xiao_d 4 GPIO_ACTIVE_LOW> // COL3 -> P0.04_A4_D4_SDA (Pin 5)
        , <&xiao_d 5 GPIO_ACTIVE_LOW> // COL4 -> P0.05_A5_D5_SCL (Pin 6)
        ;
};
